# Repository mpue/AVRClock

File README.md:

# AVRClock
A digital clock with ATMega328

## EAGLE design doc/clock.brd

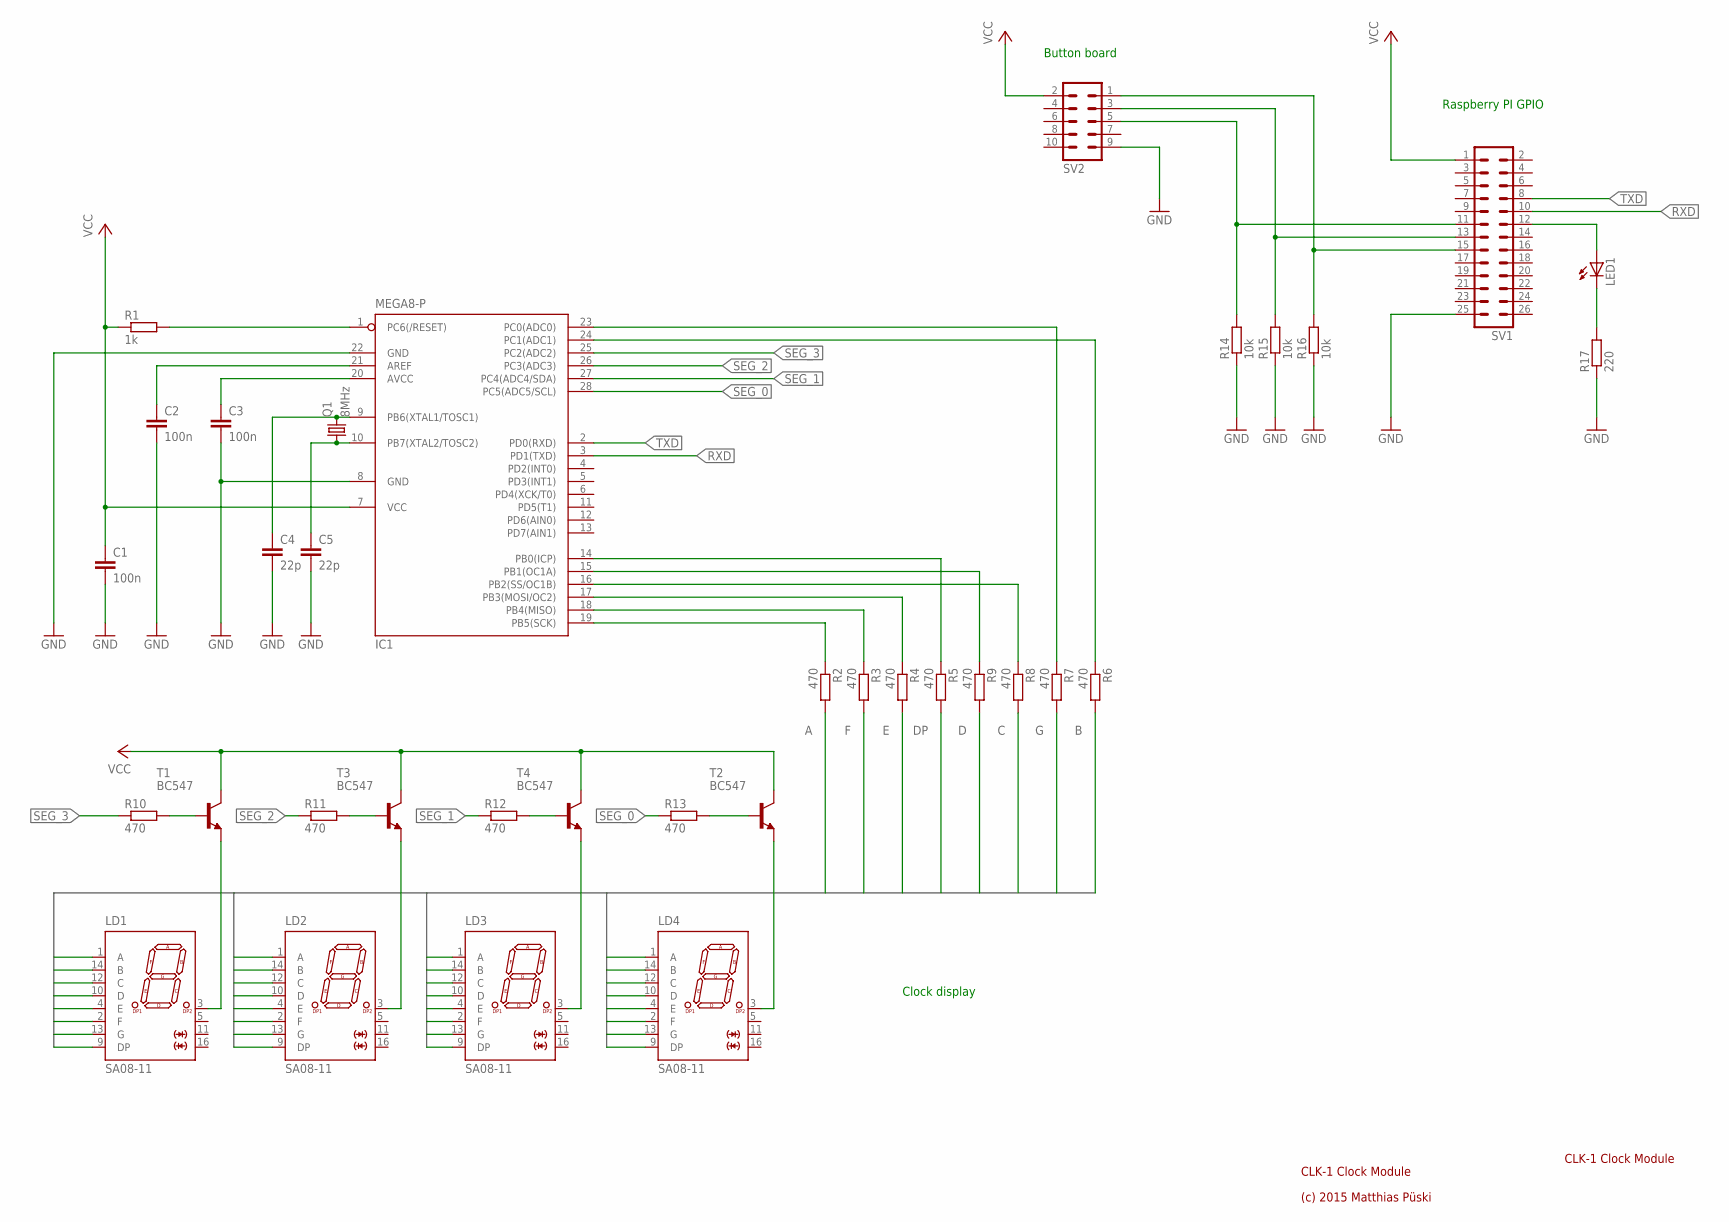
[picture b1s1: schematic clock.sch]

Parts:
C1, C2, C3: 100n; C025-024X044
C4, C5: 22p; C025-024X044
IC1: MEGA8-P; DIL28-3
LD1, LD2, LD3, LD4: SA08-11; SA08
LED1: LED5MM
Q1: 8MHz; HC49/S
R1: 1k; 0207/10
R2, R3, R4, R5, R6, R7, R8, R9, R10, R11, R12, R13: 470; 0207/10
R14, R15, R16: 10k; 0207/10
R17: 220; 0207/10
SV1: ML26L
SV2: ML10L
T1, T2, T3, T4: BC547; TO92

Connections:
A: LD1.1 (A), LD2.1 (A), LD3.1 (A), LD4.1 (A), R2.2
B: LD1.14 (B), LD2.14 (B), LD3.14 (B), LD4.14 (B), R6.2
C: LD1.12 (C), LD2.12 (C), LD3.12 (C), LD4.12 (C), R8.2
D: LD1.10 (D), LD2.10 (D), LD3.10 (D), LD4.10 (D), R9.2
DP: LD1.9 (DP), LD2.9 (DP), LD3.9 (DP), LD4.9 (DP), R5.2
E: LD1.4 (E), LD2.4 (E), LD3.4 (E), LD4.4 (E), R4.2
F: LD1.2 (F), LD2.2 (F), LD3.2 (F), LD4.2 (F), R3.2
G: LD1.13 (G), LD2.13 (G), LD3.13 (G), LD4.13 (G), R7.2
GND: C1.2, C2.2, C3.2, C4.2, C5.2, IC1.8 (GND), IC1.22 (GND), R14.1, R15.1, R16.1, R17.1, SV1.25, SV2.9
unnamed: IC1.14 (PB0(ICP)), R5.1
unnamed: IC1.18 (PB4(MISO)), R3.1
unnamed: IC1.17 (PB3(MOSI/OC2)), R4.1
unnamed: IC1.19 (PB5(SCK)), R2.1
unnamed: IC1.15 (PB1(OC1A)), R9.1
unnamed: IC1.16 (PB2(SS/OC1B)), R8.1
unnamed: IC1.23 (PC0(ADC0)), R7.1
unnamed: IC1.24 (PC1(ADC1)), R6.1
unnamed: LD1.3 (AK), T1.1 (E)
unnamed: LD2.3 (AK), T3.1 (E)
unnamed: LD3.3 (AK), T4.1 (E)
unnamed: LD4.3 (AK), T2.1 (E)
unnamed: R10.2, T1.2 (B)
unnamed: R11.2, T3.2 (B)
unnamed: R12.2, T4.2 (B)
unnamed: R13.2, T2.2 (B)
unnamed: R14.2, SV1.11, SV2.5
unnamed: R15.2, SV1.13, SV2.3
unnamed: R16.2, SV1.15, SV2.1
unnamed: LED1.A, SV1.12
unnamed: IC1.1 (PC6(/RESET)), R1.2
unnamed: LED1.K (C), R17.2
unnamed: C2.1, IC1.21 (AREF)
unnamed: C3.1, IC1.20 (AVCC)
unnamed: C4.1, IC1.9 (PB6(XTAL1/TOSC1)), Q1.2
unnamed: C5.1, IC1.10 (PB7(XTAL2/TOSC2)), Q1.1
RXD: IC1.3 (PD1(TXD)), SV1.10
SEG_0: IC1.28 (PC5(ADC5/SCL)), R13.1
SEG_1: IC1.27 (PC4(ADC4/SDA)), R12.1
SEG_2: IC1.26 (PC3(ADC3)), R11.1
SEG_3: IC1.25 (PC2(ADC2)), R10.1
TXD: IC1.2 (PD0(RXD)), SV1.8
VCC: C1.1, IC1.7 (VCC), R1.1, SV1.1, SV2.2, T1.3 (C), T2.3 (C), T3.3 (C), T4.3 (C)

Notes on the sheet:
CLK-1 Clock Module
(c) 2015 Matthias Püski
Raspberry PI GPIO
Clock display
Button board

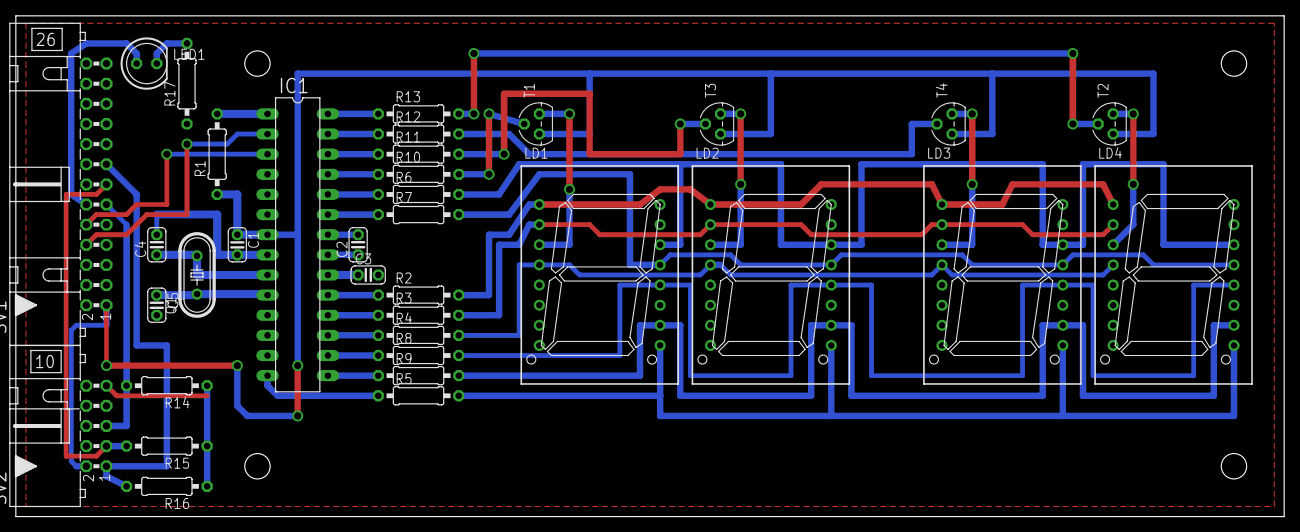
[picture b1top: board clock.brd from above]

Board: 2 copper layers, 160.0 x 63.2 mm, 35 parts (0 on the bottom side), 42 nets.

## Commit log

2015-10-24 added readme
2015-10-31 Added DCF-77 decoding
2015-10-31 date and time validation
2015-10-31 added check interval
2015-11-07 Added schematics
2015-11-09 Added serial interface
2015-12-06 Latest corrections
